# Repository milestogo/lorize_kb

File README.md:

# Lorize: a family of low profile 60% ergonomic keyboards that aren't too weird.  

These should be familiar to users of a MS natural or Sculpt keyboard, but pull in elements from the boardrun, alice, and kinesis keyboards. 
Available in desktop and MNT reform versions.

The lorize.scad file is intended to be used with the openscad configurator. You can change the type of keyboard (desktop, laptop, mutants), and the layer. The output can be used for laser cutting plate and case files. The POS files are used as an easy way to export centroid information from kicad & import into SCAD, which is used to make the bottom layer cutouts. 

lorize3 folder is for a desktop version of the PCB. it can be split for tenting, or used unsplit. This PCB can be soldered using only through hole 
techniques (no stencil).

The PCB for the laptop version is located at ,in the ergo1 branch. This was done as a remix of the original keyboard, so that the factory firmware will still work. The board was updated to be single sided to reduce cost/effort of assembly. There isn't quite enough room to fit on top to fit a pro micro, so it requires SMD work. 

#Todos.
Vertical spacing between switches is using 17mm spacing. This feels big if you use MBK or other low height keycaps.  
For ease of hand routing, the laptop PCB has some weird parts I built. The diodes could be changed & the board autorouted. 

The desktop version's RGB LEDs aren't well placed. Consider replacing with crenelated tabs to solder LED strip on the edge. . 

The laptop version doesn't have RGB LEDs,underglow would work well for the MNT case, or edge lit by the trackpad.

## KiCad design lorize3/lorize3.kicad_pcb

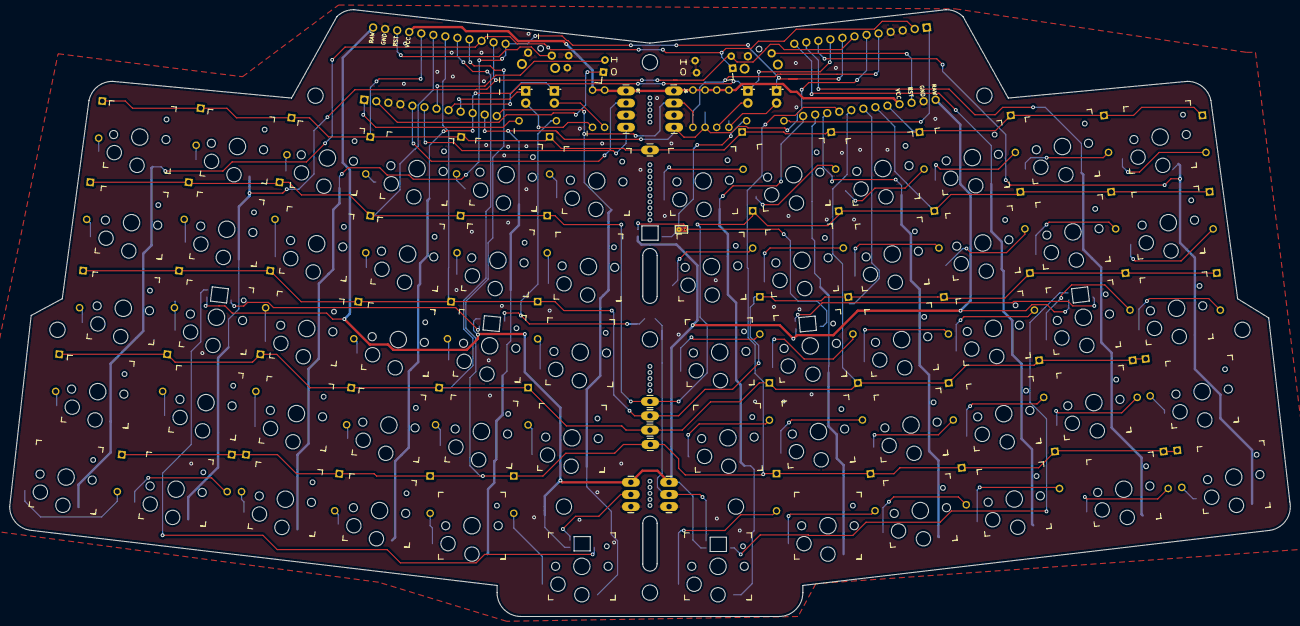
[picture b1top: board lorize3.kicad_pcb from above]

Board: 2 copper layers, 267.9 x 126.9 mm, 170 parts (1 on the bottom side), 103 nets.

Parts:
D1, D2, D3, D4, D5, D11, D12, D13, D14, D15, D21, D22, D23, D24, D25, D31, D32, D33, D34, D35, D41, D42, D43, D44, D45, D51, D52, D53, D54, D55, D61, D62, D63, D64, D65, D71, D72, D73, D74, D75, D81, D82, D83, D84, D85, D91, D92, D93, D94, D95, D101, D102, D103, D104, D105, D111, D112, D113, D114, D115: Device_D; Diode-Hybrid-Back
D201, D202, D203, D204: LED-3MM; LED_3mm_Radial
H1, H11, H12, H14, H15: Hole; breakaway-mousebites
H2, H3, H4, H5, H6, H7, H8, H9, H10: Hole; MountingHole_3.2mm_M3
J1, J2: Conn_01x03; 1X03_LONGPADS
J6, J8: Conn_01x04; 1X04_LONGPADS
JP4: Jumper_2_Bridged; ThickJumper
JP12: Jumper_2_Open; JUMPER_SMD_2DUB
L1, L2, L3, L4, L5, L7: kbd_SK6812MINI; SK6812-MINI-E
L6: kbd_SK6812MINI-E; SK6812-MINI-E
R1, R2, R3, R4, R5#2: Conn_01x01; 1X01_LONGPAD
R2#2, R3#2, R4#2, R5: 300; Resistor-Hybrid-Back
R9, R10: 4k7; Resistor-Hybrid-Back
R11, R12: 1k; Resistor-Hybrid-Back
SW1, SW2, SW3, SW4, SW5, SW11, SW12, SW13, SW14, SW15, SW21, SW22, SW23, SW24, SW25, SW31, SW32, SW33, SW34, SW35, SW41, SW42, SW43, SW44, SW45, SW51, SW52, SW53, SW54, SW55, SW61, SW62, SW63, SW64, SW65, SW71, SW72, SW73, SW74, SW75, SW81, SW82, SW83, SW84, SW85, SW91, SW92, SW93, SW94, SW95, SW101, SW102, SW103, SW104, SW105, SW111, SW112, SW113, SW114, SW115: kbd_SW_PUSH; Kailh_socket_PG1350
SW200, SW201: Reset Switch; SW_Tactile_SPST_Angled_MJTP1117
SW204, SW205: SW_DIP_x02; SW_DIP_SPSTx02_Slide_6.7x6.64mm_W7.62mm_P2.54mm_LowProfile
U1: ProMicro Left; ArduinoProMicro-notopsilk
U2: ProMicro Right; ArduinoProMicro-notopsilk

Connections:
+5V: J1.3, J2.3, L1.1, L2.1, L3.1, L4.1, L5.1, L6.1, L7.1, U1.24, U2.24
C0: SW1.1, SW2.1, SW3.1, SW4.1, SW5.1, SW205.1, U1.15, U2.2
C1: SW11.1, SW12.1, SW13.1, SW14.1, SW15.1, SW205.2, U1.14, U2.7
C2: D203.K, SW21.1, SW22.1, SW23.1, SW24.1, SW25.1, U1.13, U2.8
C3: D204.K, SW31.1, SW32.1, SW33.1, SW34.1, SW35.1, U1.10, U2.9
C4: J6.4, R10.2, SW41.1, SW42.1, SW43.1, SW44.1, SW45.1, U1.11, U2.6
C5: J6.2, R9.2, SW51.1, SW52.1, SW53.1, SW54.1, SW55.1, U1.12, U2.5
C6: SW61.1, SW62.1, SW63.1, SW64.1, SW65.1, U2.13
C7: SW71.1, SW72.1, SW73.1, SW74.1, SW75.1, U2.14
C8: SW81.1, SW82.1, SW83.1, SW84.1, SW85.1, U2.15
C9: SW91.1, SW92.1, SW93.1, SW94.1, SW95.1, U2.12
C10: SW101.1, SW102.1, SW103.1, SW104.1, SW105.1, U2.11
C11: SW111.1, SW112.1, SW113.1, SW114.1, SW115.1, U2.10
GND: J1.1, J2.1, J6.3, J8.3, L1.3, L2.3, L3.3, L4.3, L5.3, L6.3, L7.3, SW200.1, SW201.1, SW204.3, SW204.4, SW205.3, SW205.4, U1.3, U1.4, U1.23, U2.3, U2.4, U2.23
LED1: D201.K, U1.8
LED2: D202.K, U1.9
unnamed: D1.2, SW1.2
unnamed: D2.2, SW2.2
unnamed: D3.2, SW3.2
unnamed: D4.2, SW4.2
unnamed: D5.2, SW5.2
unnamed: D11.2, SW11.2
unnamed: D12.2, SW12.2
unnamed: D13.2, SW13.2
unnamed: D14.2, SW14.2
unnamed: D15.2, SW15.2
unnamed: D21.2, SW21.2
unnamed: D22.2, SW22.2
unnamed: D23.2, SW23.2
unnamed: D24.2, SW24.2
unnamed: D25.2, SW25.2
unnamed: D31.2, SW31.2
unnamed: D32.2, SW32.2
unnamed: D33.2, SW33.2
unnamed: D34.2, SW34.2
unnamed: D35.2, SW35.2
unnamed: D41.2, SW41.2
unnamed: D42.2, SW42.2
unnamed: D43.2, SW43.2
unnamed: D44.2, SW44.2
unnamed: D45.2, SW45.2
unnamed: D51.2, SW51.2
unnamed: D52.2, SW52.2
unnamed: D53.2, SW53.2
unnamed: D54.2, SW54.2
unnamed: D55.2, SW55.2
unnamed: D61.2, SW61.2
unnamed: D62.2, SW62.2
unnamed: D63.2, SW63.2
unnamed: D64.2, SW64.2
unnamed: D65.2, SW65.2
unnamed: D71.2, SW71.2
unnamed: D72.2, SW72.2
unnamed: D73.2, SW73.2
unnamed: D74.2, SW74.2
unnamed: D75.2, SW75.2
unnamed: D81.2, SW81.2
unnamed: D82.2, SW82.2
unnamed: D83.2, SW83.2
unnamed: D84.2, SW84.2
unnamed: D85.2, SW85.2
unnamed: D91.2, SW91.2
unnamed: D92.2, SW92.2
unnamed: D93.2, SW93.2
unnamed: D94.2, SW94.2
unnamed: D95.2, SW95.2
unnamed: D101.2, SW101.2
unnamed: D102.2, SW102.2
unnamed: D103.2, SW103.2
unnamed: D104.2, SW104.2
unnamed: D105.2, SW105.2
unnamed: D111.2, SW111.2
unnamed: D112.2, SW112.2
unnamed: D113.2, SW113.2
unnamed: D114.2, SW114.2
unnamed: D115.2, SW115.2
unnamed: D201.A, R3#2.1
unnamed: D202.A, R2#2.1
unnamed: D203.A, R5.1
unnamed: D204.A, R4#2.1
unnamed: J1.2, L7.2
unnamed: J2.2, JP4.2, L4.2
unnamed: JP4.1, L5.4, R12.1
unnamed: JP12.1, L1.2, L2.4
unnamed: JP12.2, L1.4, R11.1
unnamed: L2.2, L3.4
unnamed: L3.2, L4.4
unnamed: L5.2, L6.4
unnamed: L6.2, L7.4
R1: D1.1, D11.1, D21.1, D31.1, D41.1, D51.1, D61.1, D71.1, D81.1, D91.1, D101.1, D111.1, R1.1, U1.20, U2.20
R2: D2.1, D12.1, D22.1, D32.1, D42.1, D52.1, D62.1, D72.1, D82.1, D92.1, D102.1, D112.1, R2.1, U1.19, U2.19
R3: D3.1, D13.1, D23.1, D33.1, D43.1, D53.1, D63.1, D73.1, D83.1, D93.1, D103.1, D113.1, R3.1, U1.18, U2.18
R4: D4.1, D14.1, D24.1, D34.1, D44.1, D54.1, D64.1, D74.1, D84.1, D94.1, D104.1, D114.1, R4.1, U1.17, U2.17
R5: D5.1, D15.1, D25.1, D35.1, D45.1, D55.1, D65.1, D75.1, D85.1, D95.1, D105.1, D115.1, R5#2.1, U1.16, U2.16
RGB-L: R12.2, U1.1
RGB-R: R11.2, U2.1
RST-L: SW200.2, U1.22
RST-R: SW201.2, U2.22
SCL: J8.4, U1.6
SDA: J8.2, U1.5
VCC: J6.1, J8.1, R2#2.2, R3#2.2, R4#2.2, R5.2, R9.1, R10.1, U1.21, U2.21
dip1: SW204.1, U1.2
dip2: SW204.2, U1.7

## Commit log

2022-01-10 improve echo output showing component locations
2022-01-16 reduce vertical spacing of keys, automate placement from scad , switch to two 1u keys
